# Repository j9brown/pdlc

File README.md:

# PDLC driver

**Status: UNDER DEVELOPMENT**

Drives [polymer dispersed liquid crystal (PDLC) film](https://en.wikipedia.org/wiki/Smart_glass#Polymer-dispersed_liquid-crystal_devices) from a 12 V DC nominal power supply.

PDLC film is opaque when turned off and becomes clear when turned on.  For example, you can apply it to a window to replace a privacy curtain or to create a diffuse surface for a projection screen on demand.

## Features

Here are some of the features of this PDLC driver board:

- Supports approximately 4 square meters of PDLC film depending on its electrical characteristics
- Outputs ~60 V AC with up to 18 W of power from a 10 to 16 VDC power supply
- Can use a switch, relay, optocoupler, or transistor to remotely enable the driver
- Includes built-in circuit protection for the supply and load
- Power on indicator

## Design synopsis

The driver has the following major components:

- A [LM5158](https://www.ti.com/lit/ds/symlink/lm5158.pdf) boost converter produces ~60 V DC at 300 mA (actually 61 V DC) with overload, over voltage, and over temperature protection
- A [LM5108](https://www.ti.com/lit/ds/symlink/lm5108.pdf) half-bridge driver and discrete FETs produce the AC square wave output
- A [TLC555](http://www.ti.com/lit/ds/symlink/tlc555.pdf) timer and [SN74LVC1G14](https://www.ti.com/lit/ds/symlink/sn74lvc1g14.pdf) inverter generate square waves for commutation at 100 Hz
- Supply circuit protection with a 2 A polyfuse and transient voltage suppressor
- Remote enable / shutdown circuit with under voltage lock-out

[View the schematics in PDF format](hardware/pdlc.pdf)

## Circuit board

## Installation

Wire the 6-pin connector according to the labels shown on the back side of the circuit board as follows.  We recommend using crimped wire ferrules to secure stranded wires before screwing them into the terminal block.

Make sure the supply is turned off while making these connections.

Connect `12V` and one `GND` terminal to a 10 to 16 V DC supply using 20 AWG (0.5 mm^2) wire or larger.  Pay attention to the polarity: `12V` is positive and `GND` is negative.  We recommend adding a 3 A fuse or circuit breaker to protect the wiring to the device.

Connect `OUTA` and `OUTB` to the PDLC film using 22 AWG (0.3 mm^2) wire or larger.  Either terminal can be connected to the PDLC film in either orientation because the film uses AC and there is no distinct polarity.  These wires carry enough voltage to deliver a small electric shock that could be harmful to people so please ensure that the wires are adequately insulated and not exposed to touch.

Connect `EN` to one `GND` terminal via a switch circuit, via a short jumper wire, or by soldering the `ENABLE` jumper closed.  The `EN` terminal is active low so the driver turns on when `EN` is grounded and turn offs otherwise.  Use 24 AWG (0.2 mm^2) wire or larger to make the connection.  Smaller wires will work but may be too fragile for the terminals.

The switch circuit carries less than 1 mA of current at 12 V DC nominal.  You can use many kinds of switching devices to close the circuit from `EN` to `GND` such as a simple SPST rocker switch, a relay, an optocoupler, or a transistor.

If you would like to disable the power on indicator, cut the `JP1` jumper trace.

## Usage

After [installing the PDLC driver](#installation), provide power to the driver and activate the switch circuit.

If everything is working as intended, the PDLC film will become clear and the power on indicator labeled `ON` will glow red (unless it has been disabled).

If this does not happen, disconnect power then recheck your connections and the [recommended operational parameters](#recommended-operational-parameters-and-circuit-protection).

## Recommended operational parameters and circuit protection

Supply:

- Voltage: 12 V DC nominal and absolute maximum range from 10 to 16 V DC
- Wiring: minimum 20 AWG (0.5 mm²)
- Circuit protection
  - Internal: built-in 2 A polyfuse, transient voltage suppressor, reverse polarity protection, and under voltage lock-out below 9 V
  - External: add a 3 A fuse or circuit breaker to protect the wiring to the device

Load:

- Voltage: ~60 V AC square wave at 100 Hz
- Current: 300 mA maximum continous load
- Power output: 18 W maximum continuous load
- Circuit protection
  - Internal: built-in overload, over voltage, and over temperature protection
  - External: ensure wires are adequately insulated and not exposed to touch

In case of an overload such as exceeding the maximum output current or a short circuit, the power supply will hiccup until the overload condition is removed.

Please test your set up carefully if you choose to operate the PDLC driver beyond these recommendations.

## PDLC film electrical characteristics

Here is some general information about the electrical characteristics of PDLC films for which this driver was design.  If your PDLC film has significantly different electrical characteristics, please follow the tuning instructions or contact the author for advice on using this driver with your film.

The film's capacitance is proportional to its surface area, around 10 uF per square meter.  It becomes clear when charged and opaque when discharged.

The film's resistance is inversely proportional to its surface area, generally in the tens to hundreds of kiloohms.  It self-discharges rapidly and becomes opaque when power is removed.

The film's clarity increases with voltage.  It is opaque at 0 V, begins to clear around 20 to 30 V, is nearly transparent around 50 V, and becomes slightly clearer with increasing voltage.

The film must be driven with AC to produce an alternating electric field to orient the liquid crystals and it may be damaged when driven in one polarity for too long.  At very low frequencies, the film acts as a shutter.  As the frequency rises to a few hertz, the film will appear to pulse between opaque and clear states.  At higher frequencies, the film appears clear.  Mains AC frequencies (50 / 60 Hz) seem adequate.

### Modifying the drive parameters

**Caution: Modifying the driver's output voltage or frequency may damage the driver or the film!  We recommend testing your changes with a small sample of the material and a current limited bench power supply.**

To change the output frequency, remove the surface mount resistor within the block labeled `FREQ` (if there is one), then solder in a surface mount resistor of a different value or a potentiometer.  Ensure that the `FREQ` resistor value generates a frequency of at least a few hertz to prevent damage to the film.

To change the output voltage, remove the surface mount resistor labeled `FBT`, then solder in a surface mount resistor of a different value.

Refer to the [schematics](hardware/pdlc.pdf) for the formulas, footprints, and default component values.

### Data

Here's some information about PDLC films that the driver has been tested with.  

- FilmBase PDLC self-adhesive grey film
  - Operating voltage: 60 V AC (manufacturer recommendation)
  - Frequency: 50/60 Hz (manufacturer recommendation)
  - Power: < 5W / m^2 (manufacturer claim)
  - Capacitance: ~12 uF / m^2 (measured)

## Design history

v1.0: Initial prototype.  Uses a 555 timer and inverter to generate commutation waveforms.  Works well for small PDLC samples.  Can't drive larger panels without modification because it does not wait for the power-good signal to be asserted and the output capacitor to be sufficiently charged before energizing the panel so it hiccups.

## Notice

The PDLC driver software, documentation, design, and all copyright protected artifacts are released under the terms of the [MIT license](LICENSE).

The PDLC driver hardware is released under the terms of the [CERN-OHL-W license](hardware/LICENSE).

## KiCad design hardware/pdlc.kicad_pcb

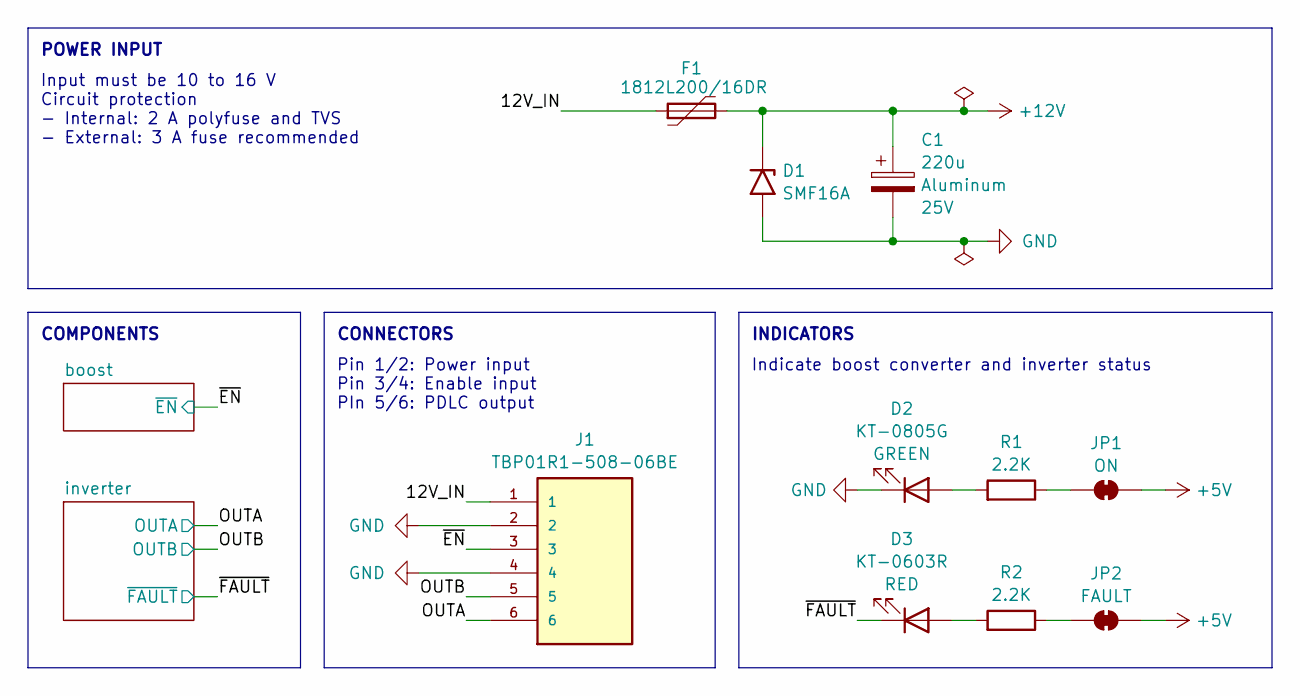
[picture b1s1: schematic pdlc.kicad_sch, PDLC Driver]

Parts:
C1: 220u; CP_Radial_D6.3mm_P2.50mm; Rating 25V; Part 2210250609R00; LCSC C2887216
D1: SMF16A; D_SMF; LCSC C207257
D2: KT-0805G; LED_0805_2012Metric; Rating GREEN; LCSC C2297
D3: KT-0603R; LED_0603_1608Metric; Rating RED; LCSC C2286
F1: 1812L200/16DR; Fuse_1812_4532Metric; LCSC C439873
J1: TBP01R1-508-06BE; CUI_TBP01R1-508-06BE
JP1, JP2: SolderJumper_2_Bridged; SolderJumper-2_P1.3mm_Bridged_RoundedPad1.0x1.5mm
R1, R2: 2.2K; R_0603_1608Metric; LCSC C4190

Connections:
+5V: JP1.1 (A), JP2.1 (A); also elsewhere on the board
+12V: C1.1, D1.1 (A1), F1.2; also elsewhere on the board
/12V_IN: F1.1, J1.1
/OUTA: J1.6; also elsewhere on the board
/OUTB: J1.5; also elsewhere on the board
/~EN: J1.3; also elsewhere on the board
/~FAULT: D3.1 (K); also elsewhere on the board
GND: C1.2, D1.2 (A2), D2.1 (K), J1.2, J1.4; also elsewhere on the board
unnamed: D2.2 (A), R1.2
unnamed: D3.2 (A), R2.2
unnamed: JP1.2 (B), R1.1
unnamed: JP2.2 (B), R2.1

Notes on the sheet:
POWER INPUT
Indicate boost converter and inverter status
CONNECTORS
INDICATORS
COMPONENTS
Pin 1/2: Power input Pin 3/4: Enable input PIn 5/6: PDLC output
Input must be 10 to 16 V Circuit protection - Internal: 2 A polyfuse and TVS - External: 3 A fuse recommended

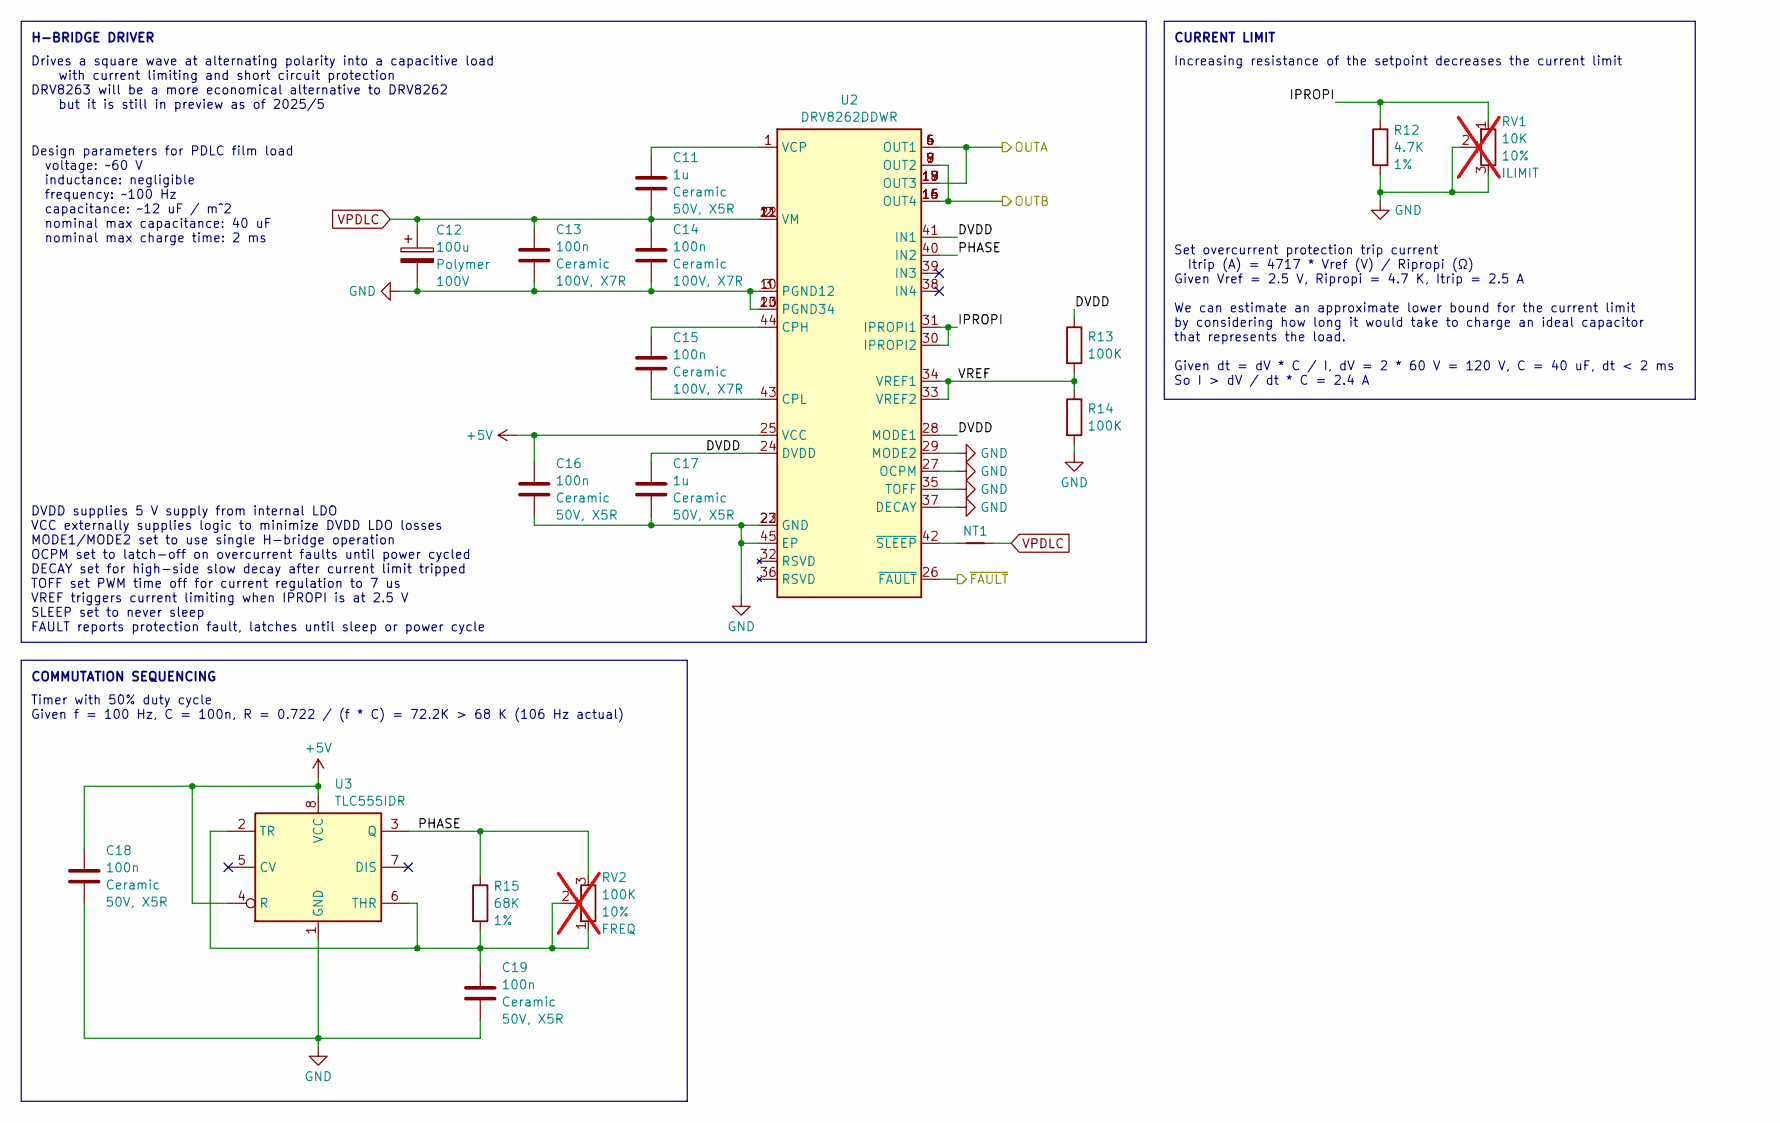
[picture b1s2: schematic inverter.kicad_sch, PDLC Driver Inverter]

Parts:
C11, C17: 1u; C_0603_1608Metric; Rating 50V, X5R; LCSC C15849
C12: 100u; CP_Radial_D10.0mm_P5.00mm; Rating 100V; Part 1011001013R00; LCSC C2887236
C13, C14, C15: 100n; C_0805_2012Metric; Rating 100V, X7R; LCSC C28233
C16, C18, C19: 100n; C_0603_1608Metric; Rating 50V, X5R; LCSC C14663
NT1: NetTie_2; NetTie-2_SMD_Pad0.2mm
R12: 4.7K; R_0603_1608Metric; Rating 1%; LCSC C23162
R13, R14: 100K; R_0603_1608Metric; LCSC C25803
R15: 68K; R_0603_1608Metric; Rating 1%; LCSC C23231
RV1: 10K; TRIM_3362P-1-502LF; Rating 10%; Part 3362P-1-103LF; not fitted
RV2: 100K; TRIM_3362P-1-502LF; Rating 10%; Part 3362P-1-104LF; not fitted
U2: DRV8262DDWR; HTSSOP-44-1EP_6.1x14mm_P0.635mm_EP5.2x14mm_Mask4.31x8.26mm; LCSC C37601386
U3: TLC555IDR; SOIC-8_3.9x4.9mm_P1.27mm; LCSC C6987

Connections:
+5V: C16.1, C18.1, U2.25 (VCC), U3.4 (R), U3.8 (VCC); also elsewhere on the board
/OUTA: U2.4 (OUT1), U2.5 (OUT1), U2.6 (OUT1), U2.17 (OUT3), U2.18 (OUT3), U2.19 (OUT3); also elsewhere on the board
/OUTB: U2.7 (OUT2), U2.8 (OUT2), U2.9 (OUT2), U2.14 (OUT4), U2.15 (OUT4), U2.16 (OUT4); also elsewhere on the board
/inverter/DVDD: C17.1, R13.1, U2.24 (DVDD), U2.28 (MODE1), U2.41 (IN1)
/inverter/IPROPI: R12.1, RV1.1, U2.30 (IPROPI2), U2.31 (IPROPI1)
/inverter/PHASE: R15.1, RV2.3, U2.40 (IN2), U3.3 (Q)
/inverter/VREF: R13.2, R14.1, U2.33 (VREF2), U2.34 (VREF1)
/~FAULT: U2.26 (~FAULT); also elsewhere on the board
GND: C12.2, C13.2, C14.2, C16.2, C17.2, C18.2, C19.2, R12.2, R14.2, RV1.2, RV1.3, U2.3 (PGND12), U2.10 (PGND12), U2.13 (PGND34), U2.20 (PGND34), U2.22 (GND), U2.23 (GND), U2.27 (OCPM), U2.29 (MODE2), U2.35 (TOFF), U2.37 (DECAY), U2.45 (EP), U3.1 (GND); also elsewhere on the board
unnamed: C15.1, U2.44 (CPH)
unnamed: C15.2, U2.43 (CPL)
unnamed: C11.1, U2.1 (VCP)
unnamed: NT1.1, U2.42 (~SLEEP)
unnamed: C19.1, R15.2, RV2.1, RV2.2, U3.2 (TR), U3.6 (THR)
VPDLC: C11.2, C12.1, C13.1, C14.1, NT1.2, U2.2 (VM), U2.11 (VM), U2.12 (VM), U2.21 (VM); also elsewhere on the board

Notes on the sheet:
Drives a square wave at alternating polarity into a capacitive load with current limiting and short circuit protection DRV8263 will be a more economical alternative to DRV8262 but it is still in preview as of 2025/5
Design parameters for PDLC film load voltage: ~60 V inductance: negligible frequency: ~100 Hz capacitance: ~12 uF / m^2 nominal max capacitance: 40 uF nominal max charge time: 2 ms
Increasing resistance of the setpoint decreases the current limit
DVDD supplies 5 V supply from internal LDO VCC externally supplies logic to minimize DVDD LDO losses MODE1/MODE2 set to use single H-bridge operation OCPM set to latch-off on overcurrent faults until power cycled DECAY set for high-side slow decay after current limit tripped TOFF set PWM time off f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
COMMUTATION SEQUENCING
Timer with 50% duty cycle Given f = 100 Hz, C = 100n, R = 0.722 / (f * C) = 72.2K > 68 K (106 Hz actual)
Set overcurrent protection trip current Itrip (A) = 4717 * Vref (V) / Ripropi (Ω) Given Vref = 2.5 V, Ripropi = 4.7 K, Itrip = 2.5 A We can estimate an approximate lower bound for the current limit by considering how long it would take to charge an ideal capacitor that represents the load. Given dt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
CURRENT LIMIT
H-BRIDGE DRIVER

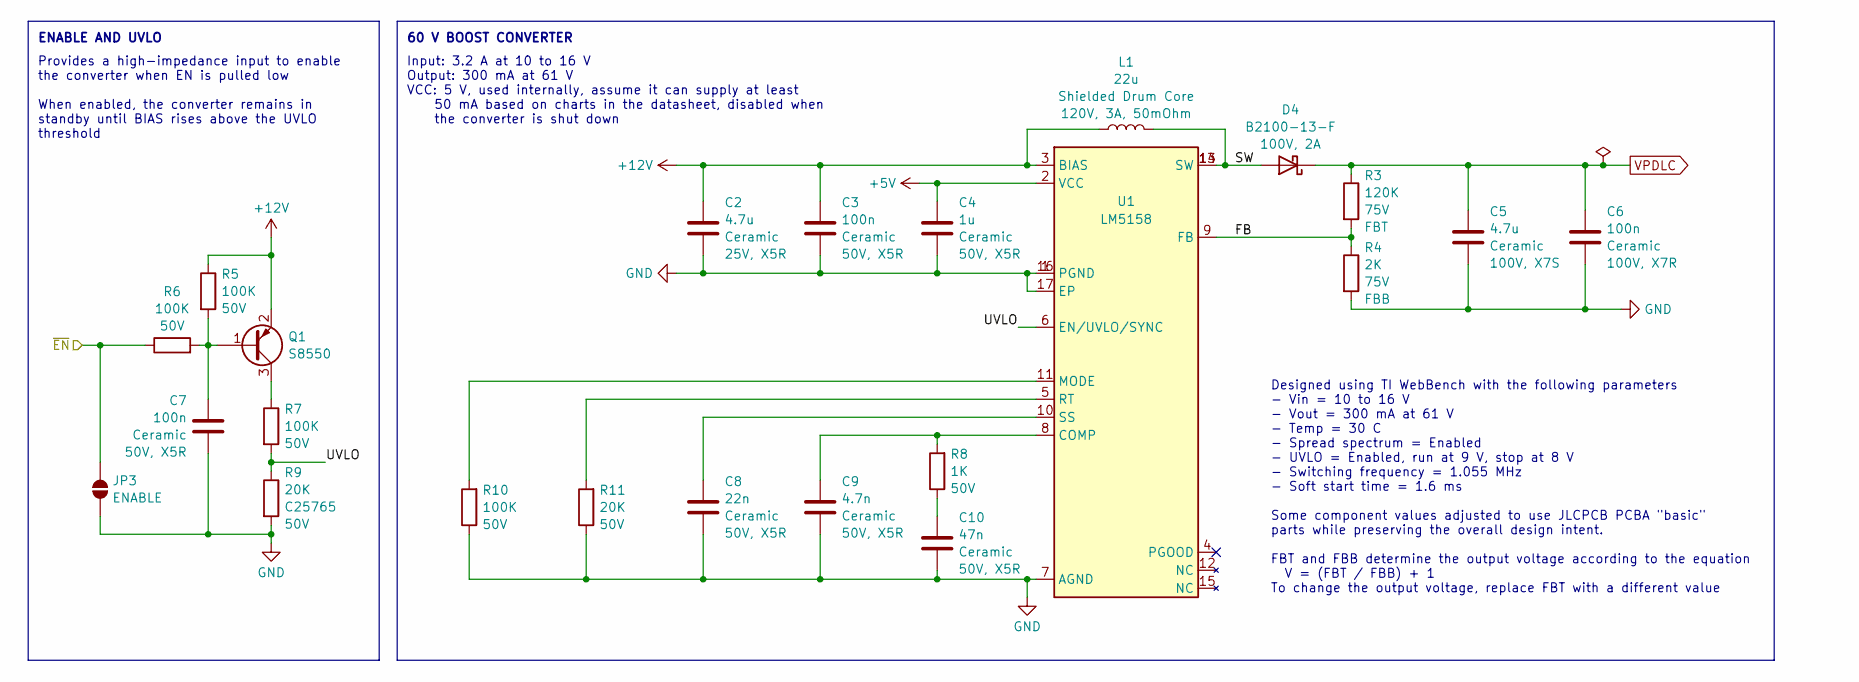
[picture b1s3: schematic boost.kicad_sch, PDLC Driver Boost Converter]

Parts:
C2: 4.7u; C_0805_2012Metric; Rating 25V, X5R; LCSC C1779
C3: 100n; C_0603_1608Metric; Rating 50V, X5R; LCSC C14663
C4: 1u; C_0603_1608Metric; Rating 50V, X5R; LCSC C15849
C5: 4.7u; C_1210_3225Metric; Rating 100V, X7S; LCSC C2803397
C6: 100n; C_0805_2012Metric; Rating 100V, X7R; LCSC C28233
C7: 100n; C_0402_1005Metric; Rating 50V, X5R; LCSC C307331
C8: 22n; C_0402_1005Metric; Rating 50V, X5R; LCSC C1532
C9: 4.7n; C_0402_1005Metric; Rating 50V, X5R; LCSC C1538
C10: 47n; C_0603_1608Metric; Rating 50V, X5R; LCSC C1622
D4: B2100-13-F; D_SMB; Rating 100V, 2A; LCSC C110479
JP3: SolderJumper_2_Open; SolderJumper-2_P1.3mm_Open_TrianglePad1.0x1.5mm
L1: 22u; WE-PD_1050P; Rating 120V, 3A, 50mOhm; Part 7447714220; LCSC C2651173
Q1: S8550; SOT-23; LCSC C105432
R3: 120K; R_0603_1608Metric; Rating 75V; LCSC C25808
R4: 2K; R_0603_1608Metric; Rating 75V; LCSC C22975
R5, R6, R7, R10: 100K; R_0402_1005Metric; Rating 50V; LCSC C25741
R8: 1K; R_0402_1005Metric; Rating 50V; LCSC C11702
R9, R11: 20K; R_0402_1005Metric; Rating 50V; LCSC C25765
U1: LM5158; LCSC C3188433

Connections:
+5V: C4.1, U1.2 (VCC); also elsewhere on the board
+12V: C2.1, C3.1, L1.1, Q1.2 (E), R5.1, U1.3 (BIAS); also elsewhere on the board
/boost/FB: R3.2, R4.1, U1.9 (FB)
/boost/SW: D4.2 (A), L1.2, U1.13 (SW), U1.14 (SW)
/boost/UVLO: R7.2, R9.1, U1.6 (EN/UVLO/SYNC)
/~EN: JP3.1 (A), R6.1; also elsewhere on the board
GND: C2.2, C3.2, C4.2, C5.2, C6.2, C7.2, C8.2, C9.2, C10.2, JP3.2 (B), R4.2, R9.2, R10.1, R11.1, U1.1 (PGND), U1.7 (AGND), U1.16 (PGND), U1.17 (EP); also elsewhere on the board
unnamed: C10.1, R8.1
unnamed: C7.1, Q1.1 (B), R5.2, R6.2
unnamed: Q1.3 (C), R7.1
unnamed: C9.1, R8.2, U1.8 (COMP)
unnamed: R10.2, U1.11 (MODE)
unnamed: R11.2, U1.5 (RT)
unnamed: C8.1, U1.10 (SS)
VPDLC: C5.1, C6.1, D4.1 (K), R3.1; also elsewhere on the board

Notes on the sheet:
60 V BOOST CONVERTER
Provides a high-impedance input to enable the converter when EN is pulled low When enabled, the converter remains in standby until BIAS rises above the UVLO threshold
Designed using TI WebBench with the following parameters - Vin = 10 to 16 V - Vout = 300 mA at 61 V - Temp = 30 C - Spread spectrum = Enabled - UVLO = Enabled, run at 9 V, stop at 8 V - Switching frequency = 1.055 MHz - Soft start time = 1.6 ms Some component values adjusted to use JLCPCB PCBA "bas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
ENABLE AND UVLO
Input: 3.2 A at 10 to 16 V Output: 300 mA at 61 V VCC: 5 V, used internally, assume it can supply at least 50 mA based on charts in the datasheet, disabled when the converter is shut down

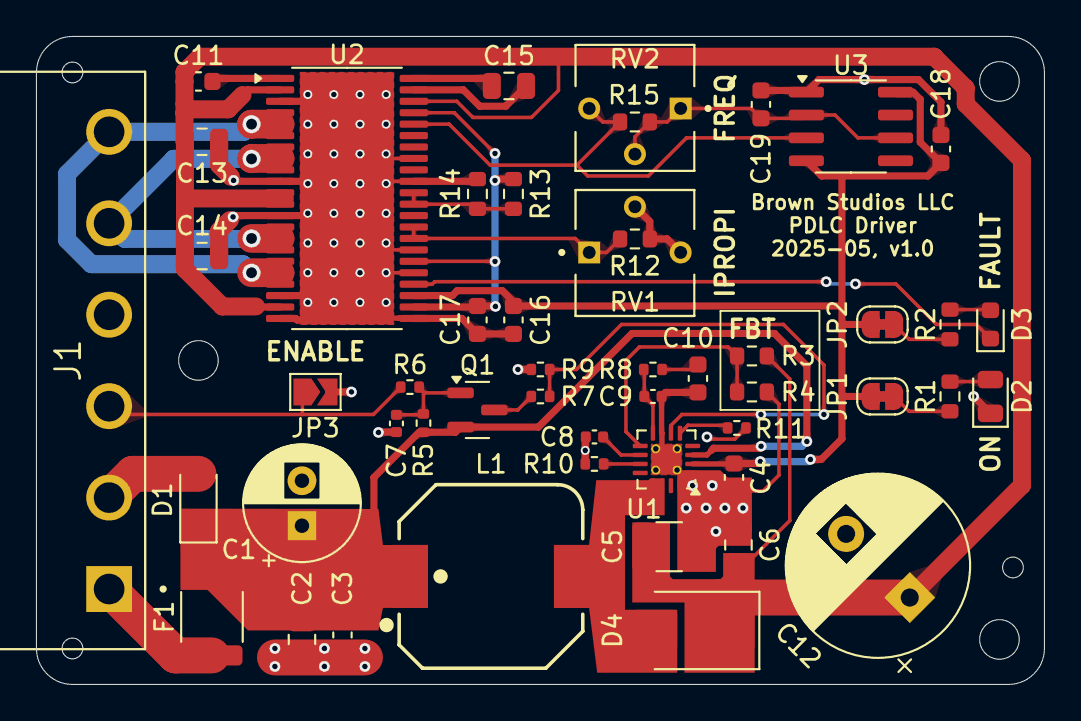
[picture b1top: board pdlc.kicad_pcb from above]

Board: 2 copper layers, 56.0 x 36.0 mm, 57 parts (0 on the bottom side), 32 nets.

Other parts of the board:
H1, H1#2, H2: MountingHole_2.2mm_M2
TH1, TH3, TH4: JLCPCB_PCBA_Tooling_Hole

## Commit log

2025-05-30 First draft using the DRV8262 H-Bridge
    This design is complete and ready for manufacture, however it has
    become clear that the DRV8262 over current protection is not compatible
    with capacitive loads because it works by engaging both high-side
    FETs which shorts the outputs. That's fine for braking an inductive
    load like a motor but it will rapidly discharge a capacitive load
    instead which is the opposite of what we're trying to do.
2025-05-30 Revised layout using LM5108 and discrete FETs
    LM5108 is less expensive but it requires more board area. In lieu of
    active current limiting, we rely on the LM5158 hiccup overload
    protection. The FETs are intentionally oversized to handle large
    current pulses when switching the polarity of the capacitive load.
    This design is complete and ready for manufacture.
2025-05-30 Always show the circuit board
2025-05-30 Recommend wires are adequately insulated and not exposed to touch
2025-05-30 Document the power on indicator
2025-06-09 Move status back to the top
2025-06-09 Ignore private files
2025-06-09 Minor project field visibility change
2025-06-12 Add design history section.
